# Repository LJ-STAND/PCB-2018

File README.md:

# PCB 2018

This repository contains the PCB design files for the LJ STAND 2018 robot. They were produced using Autodesk EAGLE.

**There are the following boards in the ```LJ STAND``` directory:**
- Encoder - this is a hall-sensor based encoder for the robot wheels. Each wheel has alternating polarity magnets that trigger the sensors.
- Gyro MPU9250 - this is a breakout board for a fusion of 3 MPU9250 sensors. This was done to compensate for drift
- Gyro - an older design of the IMU breakout board using a different sensor
- Laser Mount - mount for the laser in a light-gate module
- Light - a 48-sensor circular reflective-light sensor array, used for detecting the position of a white line
- Main - main processing board, housing the microcontrollers, camera, power supply, motor driver modules and IR sensors for the ball
- MPU9250 Adapter - can replace the IMU breakout board with a single off the shelf MPU9250 breakout
- Phototransitor Mount - mount for the phototransistor in a light-gate module

---------------------------------

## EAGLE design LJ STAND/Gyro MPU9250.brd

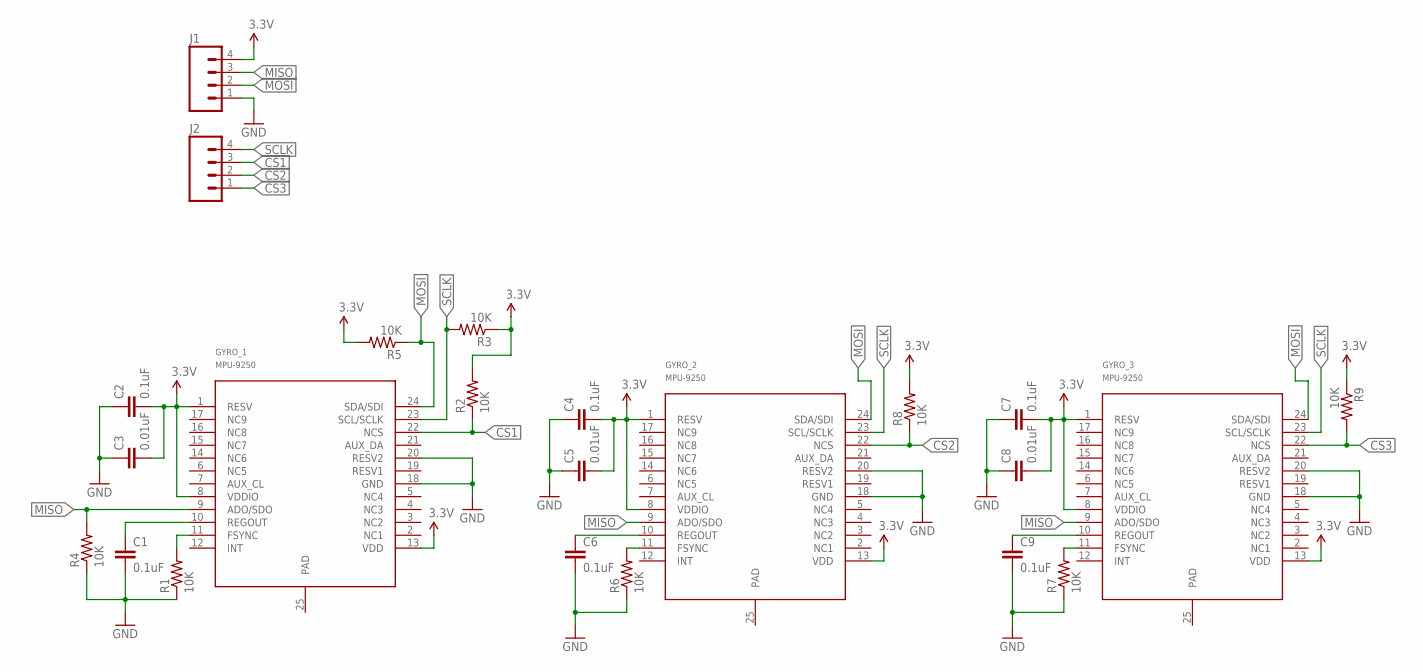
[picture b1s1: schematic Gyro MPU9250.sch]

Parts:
C1, C2, C4, C6, C7, C9: 0.1uF; 0603-CAP
C3, C5, C8: 0.01uF; 0603-CAP
GYRO_1, GYRO_2, GYRO_3: MPU-9250; LEAD-QFN24
J1, J2: M04PTH; 1X04
R1, R2, R3, R4, R5, R6, R7, R8, R9: 10K; 0603-RES

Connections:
3.3V: C2.2, C3.2, C4.2, C5.2, C7.2, C8.2, GYRO_1.1 (RESV), GYRO_1.8 (VDDIO), GYRO_1.13 (VDD), GYRO_2.1 (RESV), GYRO_2.8 (VDDIO), GYRO_2.13 (VDD), GYRO_3.1 (RESV), GYRO_3.8 (VDDIO), GYRO_3.13 (VDD), J1.4, R2.2, R3.1, R5.2, R8.2, R9.1
CS1: GYRO_1.22 (NCS), J2.3, R2.1
CS2: GYRO_2.22 (NCS), J2.2, R8.1
CS3: GYRO_3.22 (NCS), J2.1, R9.2
GND: C1.2, C2.1, C3.1, C4.1, C5.1, C6.2, C7.1, C8.1, C9.2, GYRO_1.18 (GND), GYRO_1.20 (RESV2), GYRO_2.18 (GND), GYRO_2.20 (RESV2), GYRO_3.18 (GND), GYRO_3.20 (RESV2), J1.1, R1.1, R4.1, R6.1, R7.1
MISO: GYRO_1.9 (ADO/SDO), GYRO_2.9 (ADO/SDO), GYRO_3.9 (ADO/SDO), J1.3, R4.2
MOSI: GYRO_1.24 (SDA/SDI), GYRO_2.24 (SDA/SDI), GYRO_3.24 (SDA/SDI), J1.2, R5.1
unnamed: C1.1, GYRO_1.10 (REGOUT)
unnamed: GYRO_1.11 (FSYNC), R1.2
unnamed: GYRO_3.11 (FSYNC), R7.2
unnamed: C6.1, GYRO_2.10 (REGOUT)
unnamed: C9.1, GYRO_3.10 (REGOUT)
unnamed: GYRO_2.11 (FSYNC), R6.2
SCLK: GYRO_1.23 (SCL/SCLK), GYRO_2.23 (SCL/SCLK), GYRO_3.23 (SCL/SCLK), J2.4, R3.2

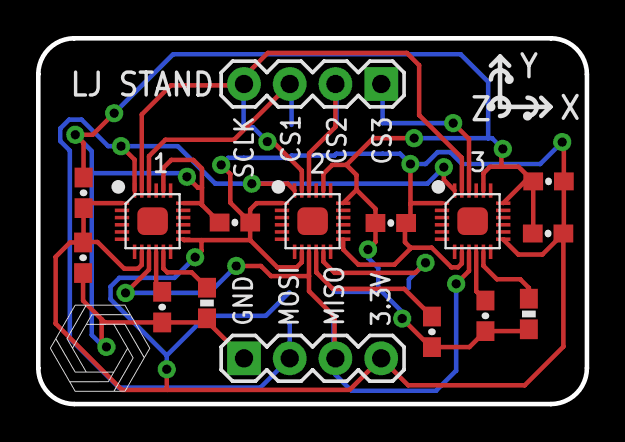
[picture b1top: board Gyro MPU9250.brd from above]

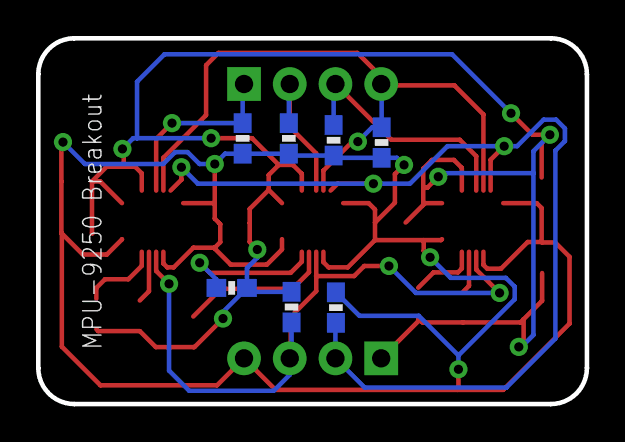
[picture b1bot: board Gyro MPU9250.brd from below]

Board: 2 copper layers, 30.5 x 20.3 mm, 23 parts (7 on the bottom side), 14 nets.

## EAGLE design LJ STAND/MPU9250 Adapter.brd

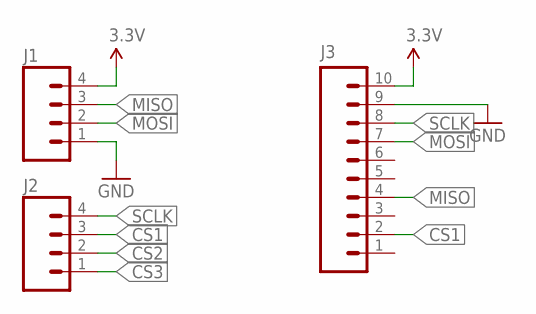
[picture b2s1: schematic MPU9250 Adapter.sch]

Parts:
J1, J2: M04PTH; 1X04
J3: M10SILK_FEMALE_PTH; 1X10

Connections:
3.3V: J1.4, J3.10
CS1: J2.3, J3.2
CS2: J2.2
CS3: J2.1
GND: J1.1, J3.9
MISO: J1.3, J3.4
MOSI: J1.2, J3.7
SCLK: J2.4, J3.8

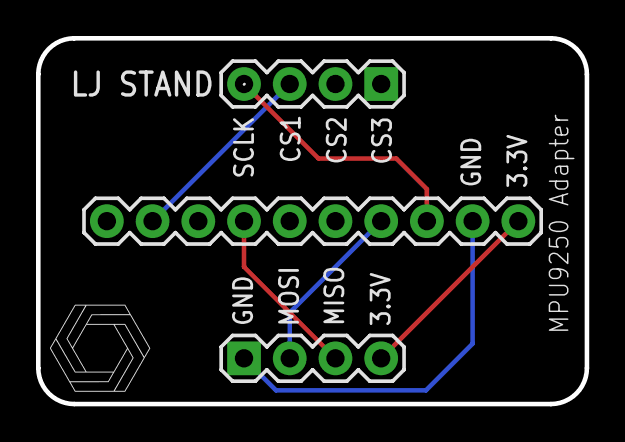
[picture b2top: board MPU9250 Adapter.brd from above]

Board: 2 copper layers, 30.5 x 20.3 mm, 3 parts (0 on the bottom side), 6 nets.

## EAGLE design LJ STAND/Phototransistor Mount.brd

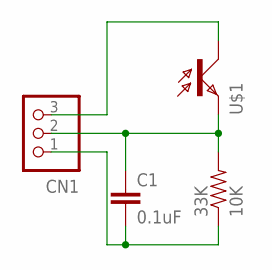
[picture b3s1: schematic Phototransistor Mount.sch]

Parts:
33K: 10K; 0603-RES
C1: 0.1uF; 0603-CAP
CN1: B3B-PH-K-S
U$1: ALS; SMD

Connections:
unnamed: CN1.3, U$1.C
unnamed: 33K.1, C1.2, CN1.1
OUT: 33K.2, C1.1, CN1.2, U$1.E

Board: 2 copper layers, 4 parts (0 on the bottom side), 3 nets, no tracks yet.

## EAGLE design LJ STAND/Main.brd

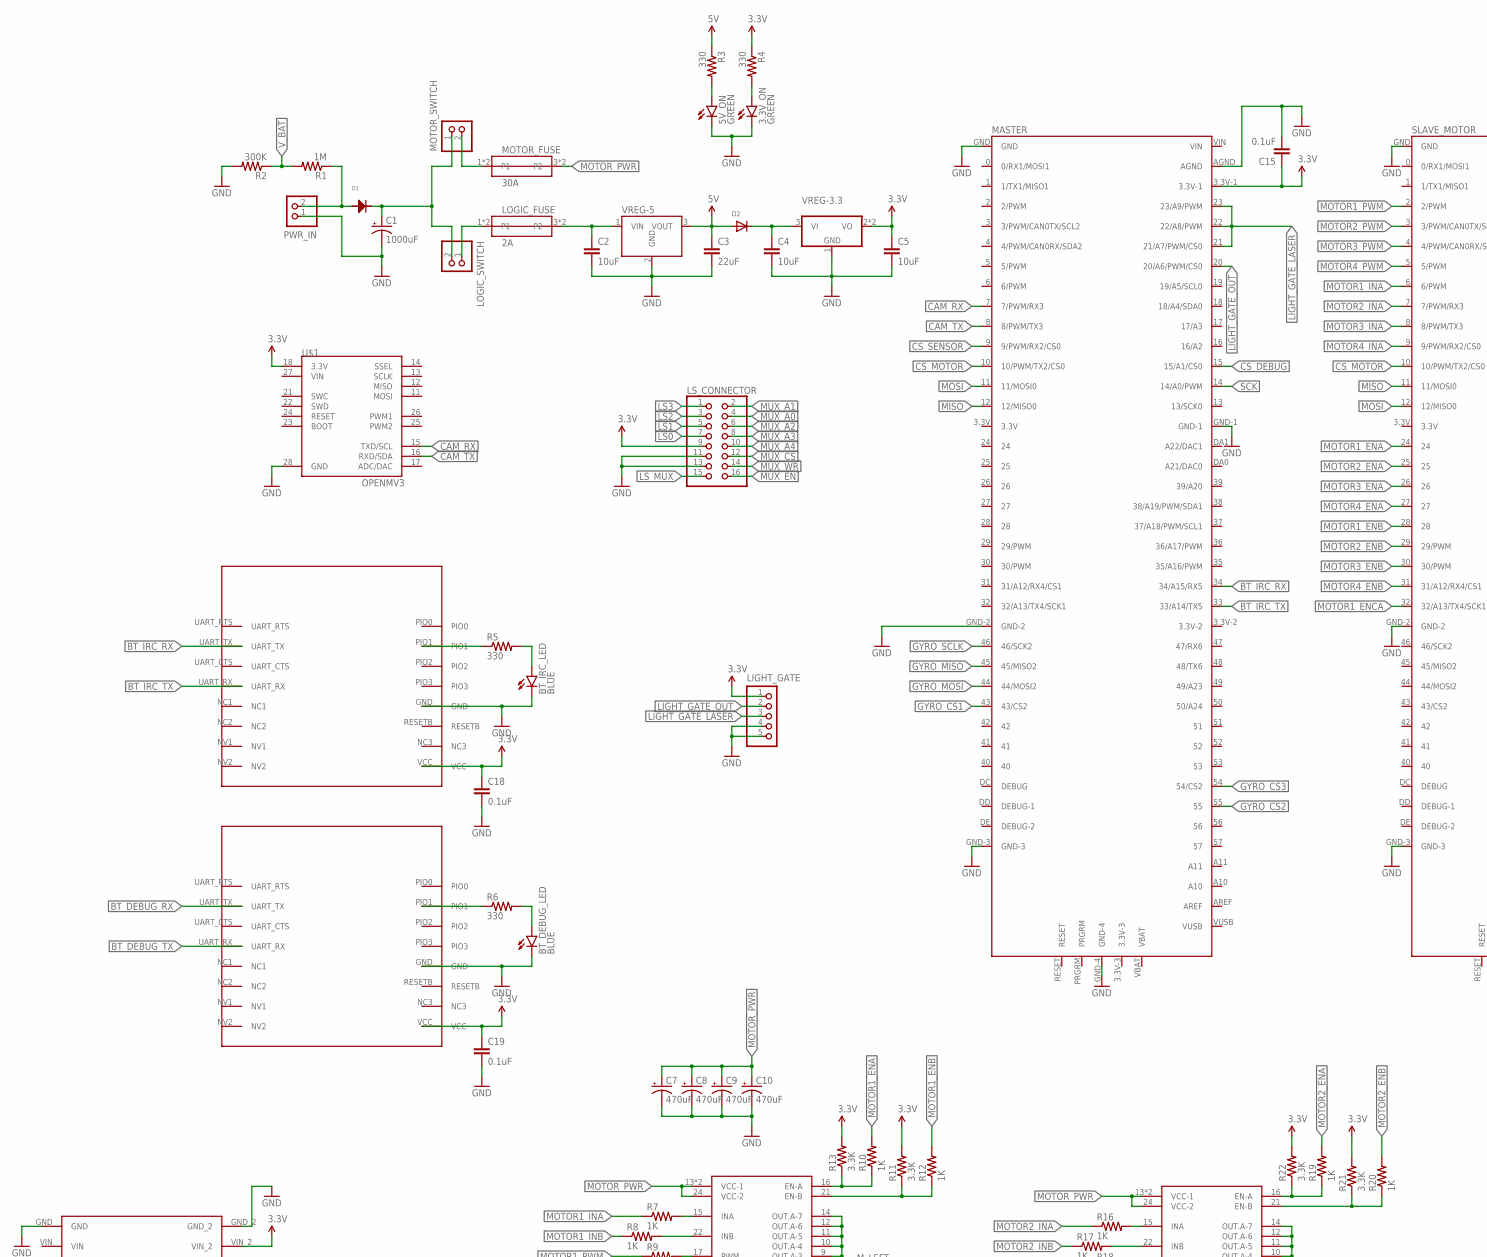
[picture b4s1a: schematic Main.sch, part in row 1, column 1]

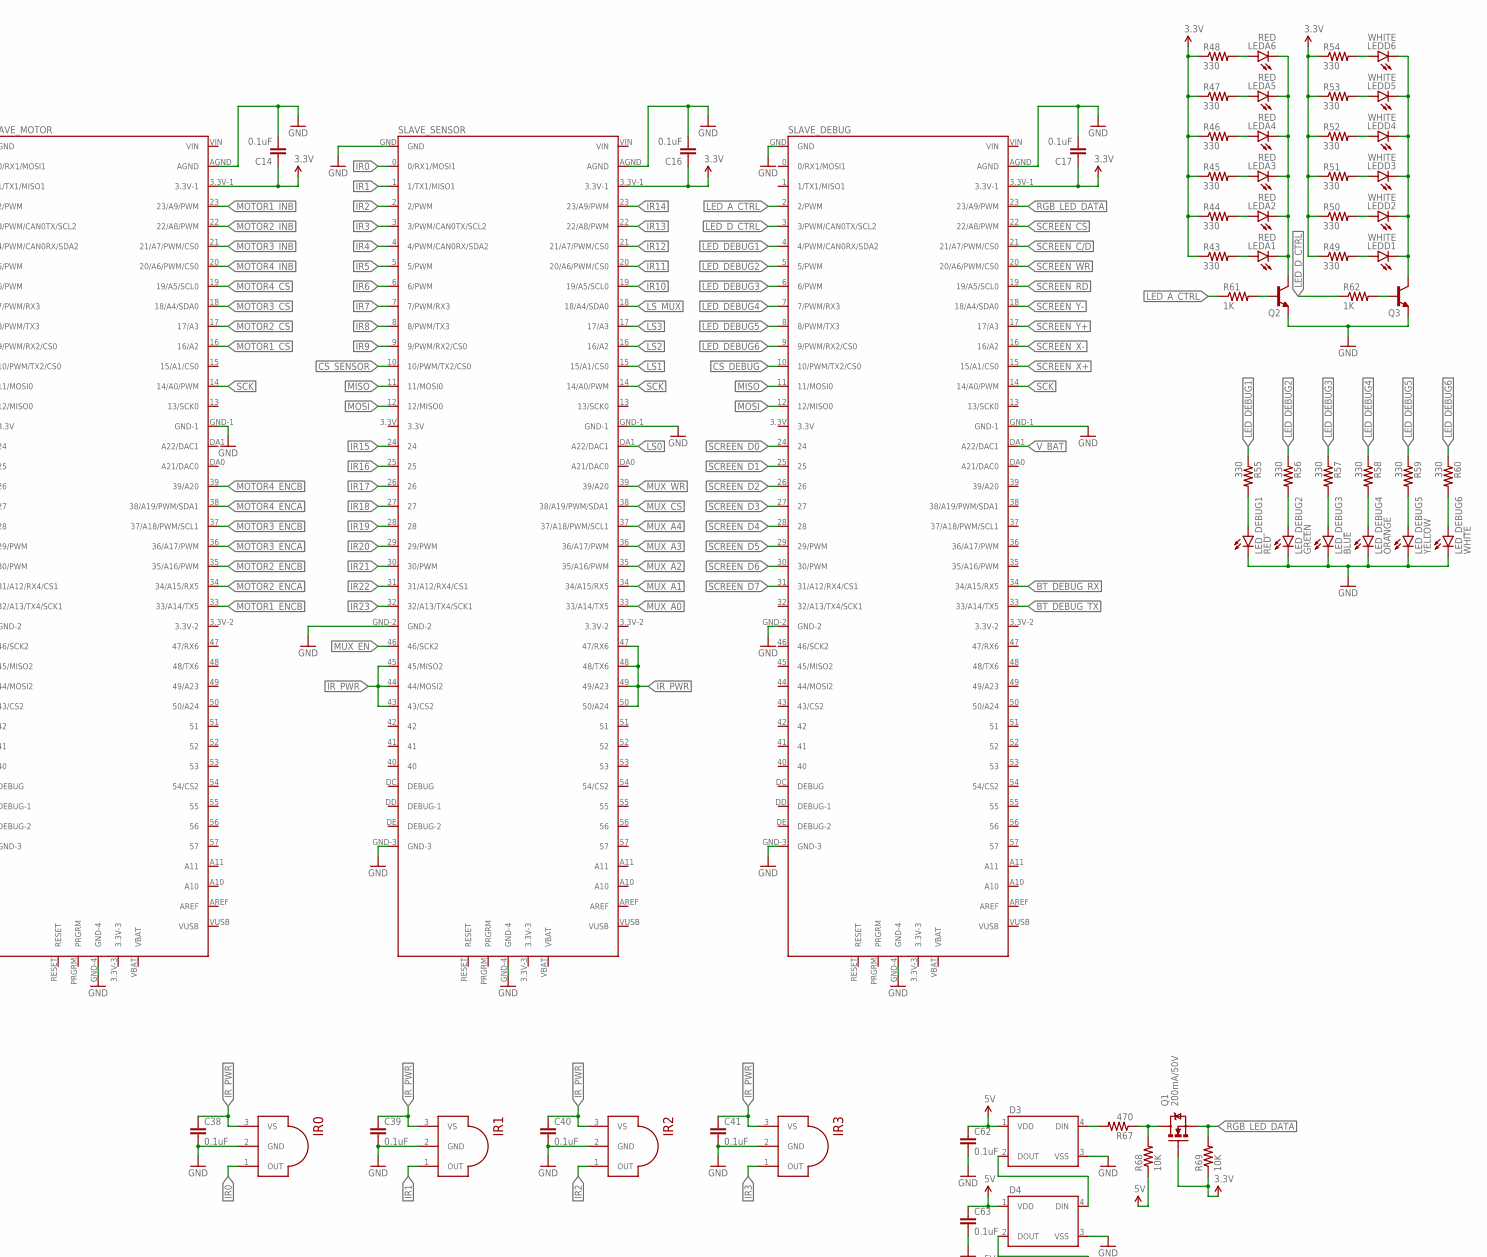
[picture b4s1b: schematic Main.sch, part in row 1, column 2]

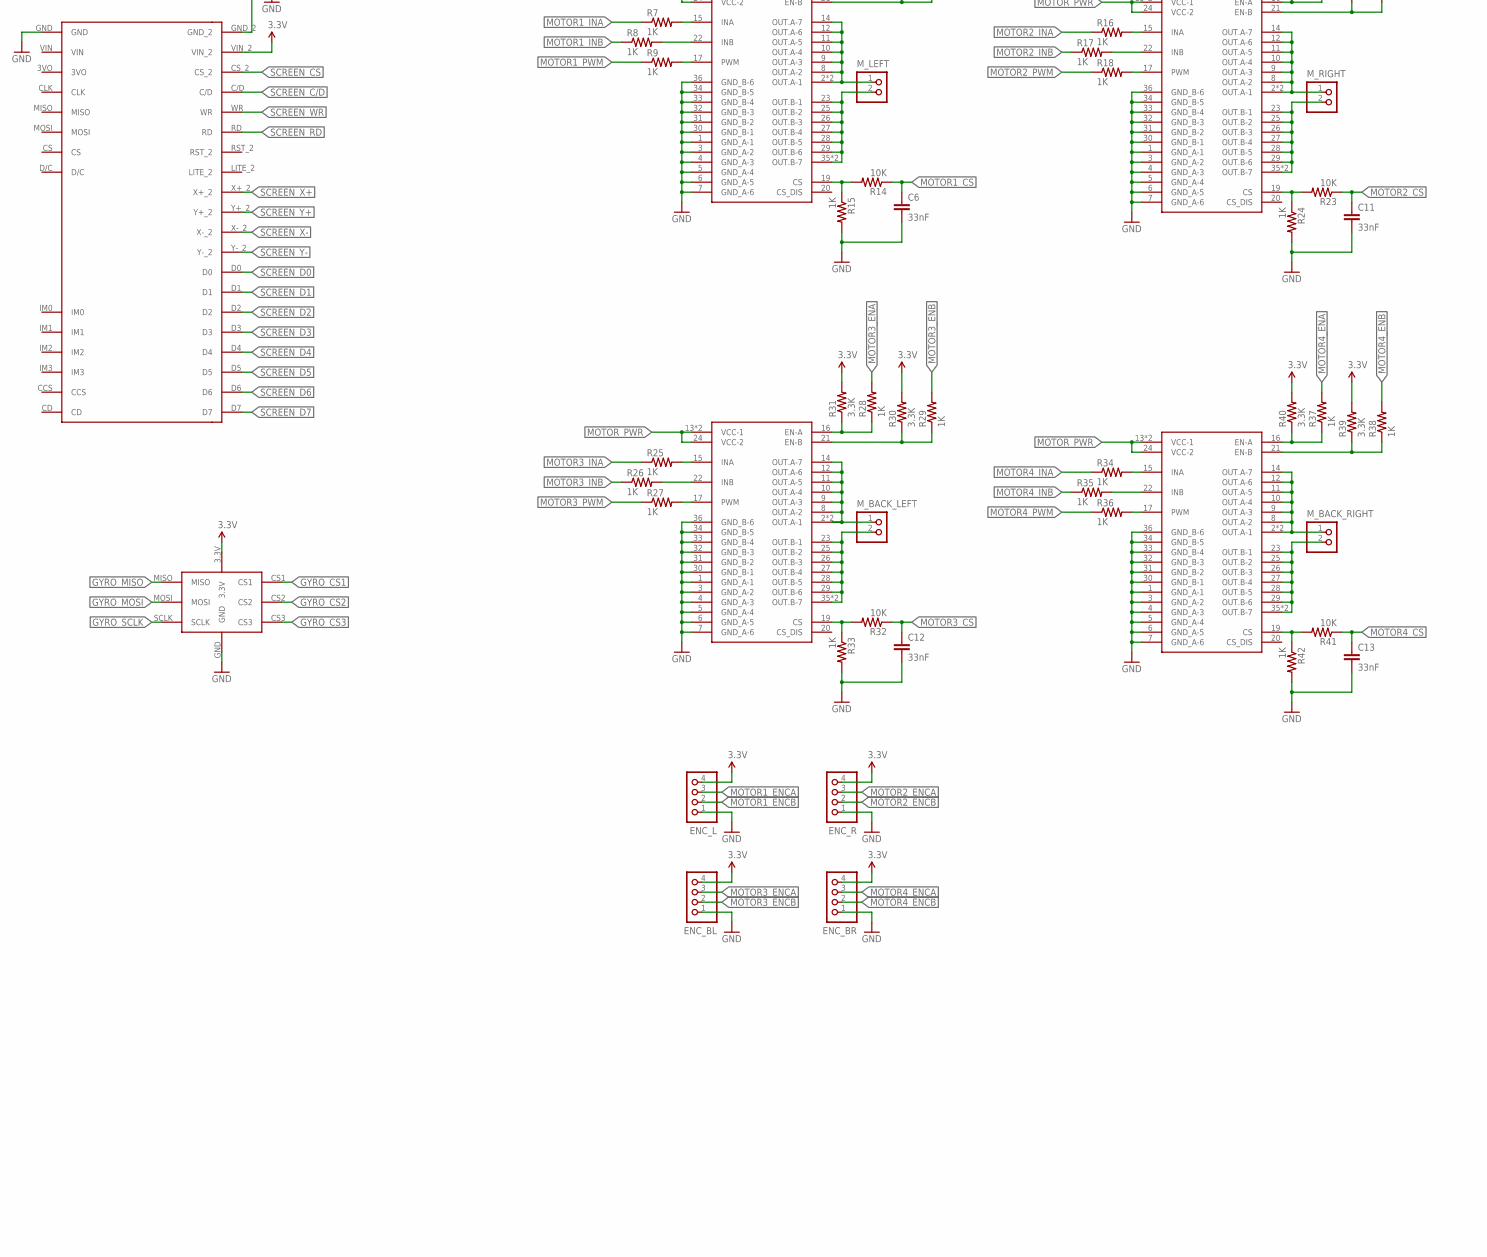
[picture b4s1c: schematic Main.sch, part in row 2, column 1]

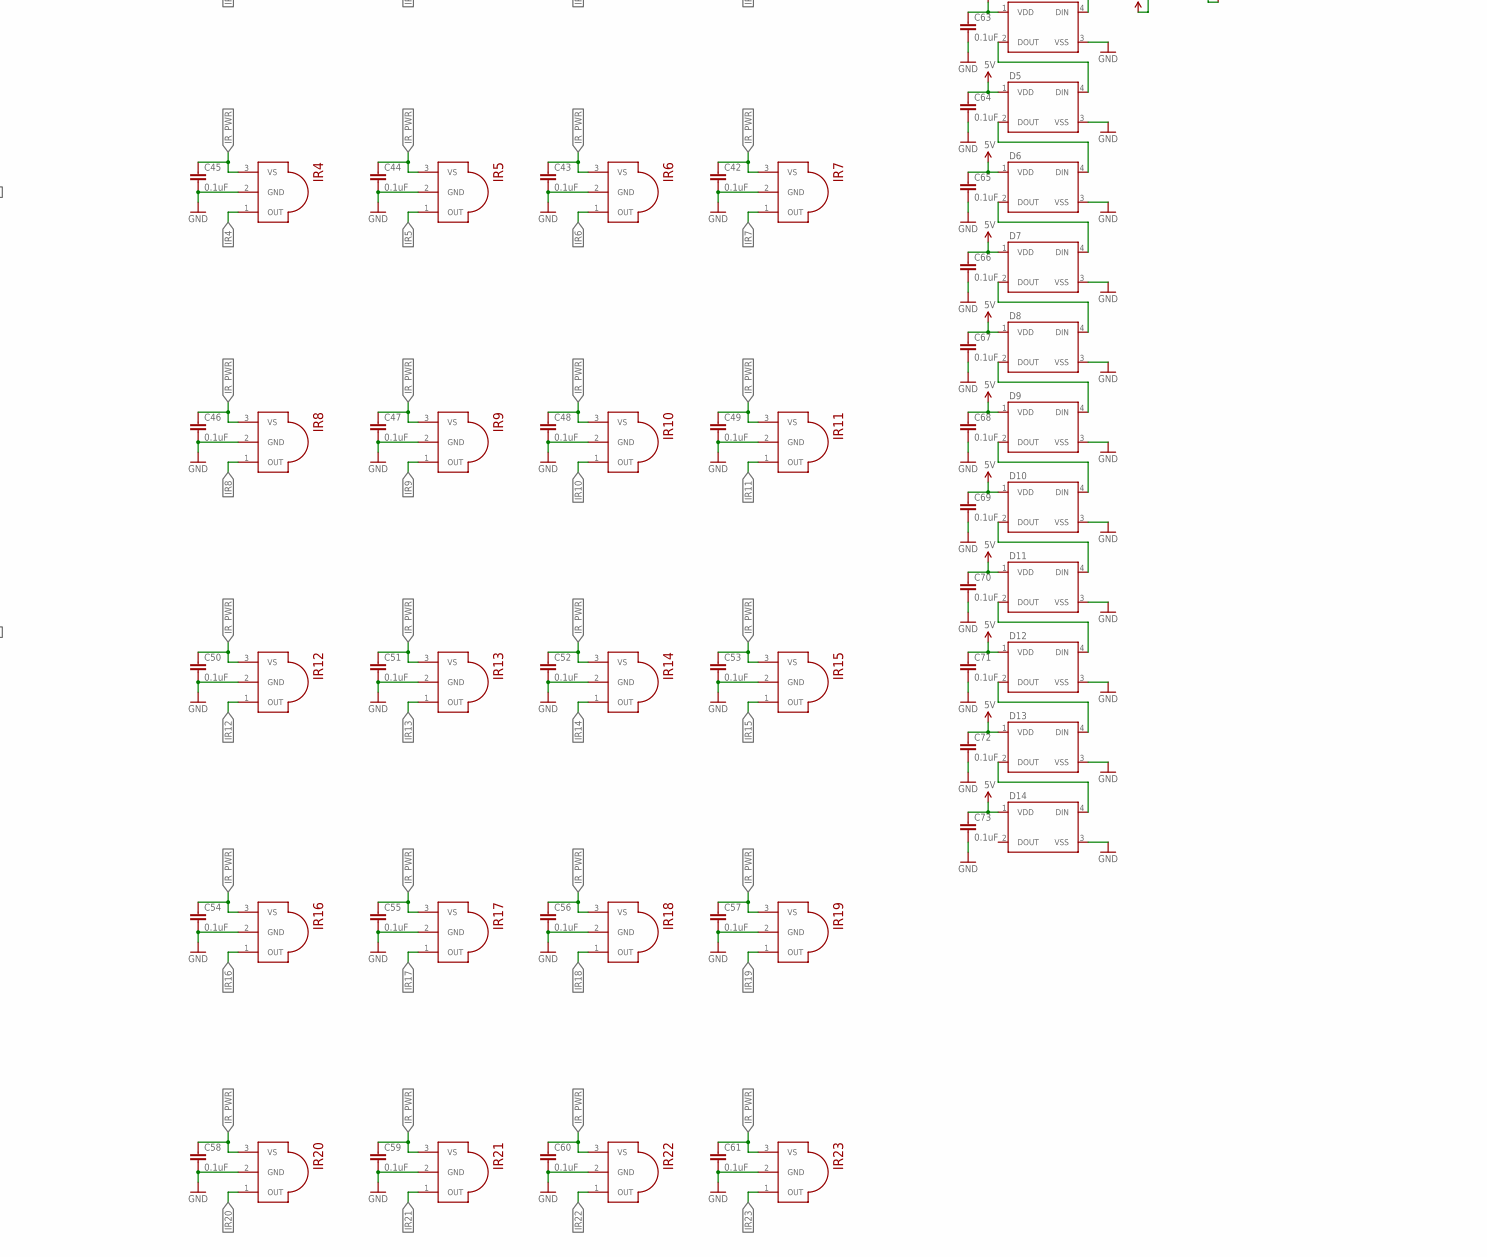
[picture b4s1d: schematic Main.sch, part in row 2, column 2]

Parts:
3.3V_ON, 5V_ON: GREEN; LED-0603
BT_DEBUG: HM-11
BT_DEBUG_LED: BLUE; LED-0603
BT_IRC: HM-11
BT_IRC_LED: BLUE; LED-0603
C1: 1000uF; CPOL-RADIAL-1000UF-25V-KIT
C2, C4, C5: 10uF; 0805
C3: 22uF; 1206
C6, C11, C12, C13: 33nF; 0603-CAP
C7, C8, C9, C10: 470uF; E3,5-8
C14, C15, C16, C17, C18, C19, C38, C39, C40, C41, C42, C43, C44, C45, C46, C47, C48, C49, C50, C51, C52, C53, C54, C55, C56, C57, C58, C59, C60, C61, C62, C63, C64, C65, C66, C67, C68, C69, C70, C71, C72, C73: 0.1uF; 0603-CAP
D1: DIODE_D2PAK(TO-263AB); D2PAK(TO-263AB)
D2: DIODE_SOD-123FL; SOD-123FL
D3, D4, D5, D6, D7, D8, D9, D10, D11, D12, D13, D14: WS2812B
ENC_BL: B4B-PH-K-S
ENC_BR: B4B-PH-K-S
ENC_L: B4B-PH-K-S
ENC_R: B4B-PH-K-S
IR0, IR1, IR2, IR3, IR4, IR5, IR6, IR7, IR8, IR9, IR10, IR11, IR12, IR13, IR14, IR15, IR16, IR17, IR18, IR19, IR20, IR21, IR22, IR23: TSSP58038
LEDA1, LEDA2, LEDA3, LEDA4, LEDA5, LEDA6: RED; LED-0603
LEDD1, LEDD2, LEDD3, LEDD4, LEDD5, LEDD6: WHITE; LED-0603
LED_DEBUG1: RED; LED-0603
LED_DEBUG2: GREEN; LED-0603
LED_DEBUG3: BLUE; LED-0603
LED_DEBUG4: ORANGE; LED-0603
LED_DEBUG5: YELLOW; LED-0603
LED_DEBUG6: WHITE; LED-0603
LIGHT_GATE: B5B-PH-K-S
LOGIC_FUSE: 2A; 3568-FUSEHOLDER
LOGIC_SWITCH: B2P-VH
LS_CONNECTOR: PINHD-2X8SMT; 2X08_SMT
MASTER: TEENSY-3.5
MOTOR_FUSE: 30A; 3568-FUSEHOLDER
MOTOR_SWITCH: B2P-VH
M_BACK_LEFT: B2P-VH
M_BACK_RIGHT: B2P-VH
M_LEFT: B2P-VH
M_RIGHT: B2P-VH
P1, P2, P3, P4: SOP50P1030X247-36N
PWR_IN: B2P-VH
Q1: 200mA/50V; SOT23-3
Q2, Q3: TRANSISTOR_NPNSOT23-3; SOT23-3
R1: 1M; 0603-RES
R2: 300K; 0603-RES
R3, R4, R5, R6, R43, R44, R45, R46, R47, R48, R49, R50, R51, R52, R53, R54, R55, R56, R57, R58, R59, R60: 330; 0603-RES
R7, R8, R9, R10, R12, R15, R16, R17, R18, R19, R20, R24, R25, R26, R27, R28, R29, R33, R34, R35, R36, R37, R38, R42, R61, R62: 1K; 0603-RES
R11, R13, R21, R22, R30, R31, R39, R40: 3.3K; 0603-RES
R14, R23, R32, R41, R68, R69: 10K; 0603-RES
R67: 470; 0603-RES
SCREEN: ADAFRUIT-2.4-TFT
SLAVE_DEBUG: TEENSY-3.5
SLAVE_MOTOR: TEENSY-3.5
SLAVE_SENSOR: TEENSY-3.5
U$1: OPENMV3
U$2: GYRO
VREG-3.3: LM340S-05; TO263-3
VREG-5: V78-2000

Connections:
3.3V: BT_DEBUG.VCC, BT_IRC.VCC, C5.1, C14.1, C15.1, C16.1, C17.1, C18.1, C19.1, ENC_BL.4, ENC_BR.4, ENC_L.4, ENC_R.4, LIGHT_GATE.1, LS_CONNECTOR.9, MASTER.3.3V-1, Q1.1 (G), R4.1, R11.2, R13.2, R21.2, R22.2, R30.2, R31.2, R39.2, R40.2, R43.1, R44.1, R45.1, R46.1, R47.1, R48.1, R49.1, R50.1, R51.1, R52.1, R53.1, R54.1, R69.1, SCREEN.VIN_2, SLAVE_DEBUG.3.3V-1, SLAVE_MOTOR.3.3V-1, SLAVE_SENSOR.3.3V-1, U$1.18 (3.3V), U$2.3.3V, VREG-3.3.2 (VO), VREG-3.3.TAB (VO)
5V: C3.1, C62.1, C63.1, C64.1, C65.1, C66.1, C67.1, C68.1, C69.1, C70.1, C71.1, C72.1, C73.1, D2.A, D3.1 (VDD), D4.1 (VDD), D5.1 (VDD), D6.1 (VDD), D7.1 (VDD), D8.1 (VDD), D9.1 (VDD), D10.1 (VDD), D11.1 (VDD), D12.1 (VDD), D13.1 (VDD), D14.1 (VDD), R3.1, R68.1, VREG-5.3 (VOUT)
BT_DEBUG_RX: BT_DEBUG.UART_TX, SLAVE_DEBUG.34 (34/A15/RX5)
BT_DEBUG_TX: BT_DEBUG.UART_RX, SLAVE_DEBUG.33 (33/A14/TX5)
BT_IRC_RX: BT_IRC.UART_TX, MASTER.34 (34/A15/RX5)
BT_IRC_TX: BT_IRC.UART_RX, MASTER.33 (33/A14/TX5)
CAM_RX: MASTER.7 (7/PWM/RX3), U$1.15 (TXD/SCL)
CAM_TX: MASTER.8 (8/PWM/TX3), U$1.16 (RXD/SDA)
CS_DEBUG: MASTER.15 (15/A1/CS0), SLAVE_DEBUG.10 (10/PWM/TX2/CS0)
CS_MOTOR: MASTER.10 (10/PWM/TX2/CS0), SLAVE_MOTOR.10 (10/PWM/TX2/CS0)
CS_SENSOR: MASTER.9 (9/PWM/RX2/CS0), SLAVE_SENSOR.10 (10/PWM/TX2/CS0)
GND: 3.3V_ON.C, 5V_ON.C, BT_DEBUG.GND, BT_DEBUG_LED.C, BT_IRC.GND, BT_IRC_LED.C, C1.-, C2.2, C3.2, C4.2, C5.2, C6.2, C7.-, C8.-, C9.-, C10.-, C11.2, C12.2, C13.2, C14.2, C15.2, C16.2, C17.2, C18.2, C19.2, C38.2, C39.2, C40.2, C41.2, C42.2, C43.2, C44.2, C45.2, C46.2, C47.2, C48.2, C49.2, C50.2, C51.2, C52.2, C53.2, C54.2, C55.2, C56.2, C57.2, C58.2, C59.2, C60.2, C61.2, C62.2, C63.2, C64.2, C65.2, C66.2, C67.2, C68.2, C69.2, C70.2, C71.2, C72.2, C73.2, D3.3 (VSS), D4.3 (VSS), D5.3 (VSS), D6.3 (VSS), D7.3 (VSS), D8.3 (VSS), D9.3 (VSS), D10.3 (VSS), D11.3 (VSS), D12.3 (VSS), D13.3 (VSS), D14.3 (VSS), ENC_BL.1, ENC_BR.1, ENC_L.1, ENC_R.1, IR0.2 (GND), IR1.2 (GND), IR2.2 (GND), IR3.2 (GND), IR4.2 (GND), IR5.2 (GND), IR6.2 (GND), IR7.2 (GND), IR8.2 (GND), IR9.2 (GND), IR10.2 (GND), IR11.2 (GND), IR12.2 (GND), IR13.2 (GND), IR14.2 (GND), IR15.2 (GND), IR16.2 (GND), IR17.2 (GND), IR18.2 (GND), IR19.2 (GND), IR20.2 (GND), IR21.2 (GND), IR22.2 (GND), IR23.2 (GND), LED_DEBUG1.C, LED_DEBUG2.C, LED_DEBUG3.C, LED_DEBUG4.C, LED_DEBUG5.C, LED_DEBUG6.C, LIGHT_GATE.4, LIGHT_GATE.5, LS_CONNECTOR.11, LS_CONNECTOR.13, MASTER.AGND, MASTER.GND, MASTER.GND-1, MASTER.GND-2, MASTER.GND-3, MASTER.GND-4, P1.1 (GND_A-1), P1.3 (GND_A-2), P1.4 (GND_A-3), P1.5 (GND_A-4), P1.6 (GND_A-5), P1.7 (GND_A-6), P1.30 (GND_B-1), P1.31 (GND_B-2), P1.32 (GND_B-3), P1.33 (GND_B-4), P1.34 (GND_B-5), P1.36 (GND_B-6), P2.1 (GND_A-1), P2.3 (GND_A-2), P2.4 (GND_A-3), P2.5 (GND_A-4), P2.6 (GND_A-5), P2.7 (GND_A-6), P2.30 (GND_B-1), P2.31 (GND_B-2), P2.32 (GND_B-3), P2.33 (GND_B-4), P2.34 (GND_B-5)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
GYRO_CS1: MASTER.43 (43/CS2), U$2.CS1
GYRO_CS2: MASTER.55, U$2.CS2
GYRO_CS3: MASTER.54 (54/CS2), U$2.CS3
GYRO_MISO: MASTER.45 (45/MISO2), U$2.MISO
GYRO_MOSI: MASTER.44 (44/MOSI2), U$2.MOSI
GYRO_SCLK: MASTER.46 (46/SCK2), U$2.SCLK
IR0: IR0.1 (OUT), SLAVE_SENSOR.0 (0/RX1/MOSI1)
IR1: IR1.1 (OUT), SLAVE_SENSOR.1 (1/TX1/MISO1)
IR2: IR2.1 (OUT), SLAVE_SENSOR.2 (2/PWM)
IR3: IR3.1 (OUT), SLAVE_SENSOR.3 (3/PWM/CAN0TX/SCL2)
IR4: IR4.1 (OUT), SLAVE_SENSOR.4 (4/PWM/CAN0RX/SDA2)
IR5: IR5.1 (OUT), SLAVE_SENSOR.5 (5/PWM)
IR6: IR6.1 (OUT), SLAVE_SENSOR.6 (6/PWM)
IR7: IR7.1 (OUT), SLAVE_SENSOR.7 (7/PWM/RX3)
IR8: IR8.1 (OUT), SLAVE_SENSOR.8 (8/PWM/TX3)
IR9: IR9.1 (OUT), SLAVE_SENSOR.9 (9/PWM/RX2/CS0)
IR10: IR10.1 (OUT), SLAVE_SENSOR.19 (19/A5/SCL0)
IR11: IR11.1 (OUT), SLAVE_SENSOR.20 (20/A6/PWM/CS0)
IR12: IR12.1 (OUT), SLAVE_SENSOR.21 (21/A7/PWM/CS0)
IR13: IR13.1 (OUT), SLAVE_SENSOR.22 (22/A8/PWM)
IR14: IR14.1 (OUT), SLAVE_SENSOR.23 (23/A9/PWM)
IR15: IR15.1 (OUT), SLAVE_SENSOR.24
IR16: IR16.1 (OUT), SLAVE_SENSOR.25
IR17: IR17.1 (OUT), SLAVE_SENSOR.26
IR18: IR18.1 (OUT), SLAVE_SENSOR.27
IR19: IR19.1 (OUT), SLAVE_SENSOR.28
IR20: IR20.1 (OUT), SLAVE_SENSOR.29 (29/PWM)
IR21: IR21.1 (OUT), SLAVE_SENSOR.30 (30/PWM)
IR22: IR22.1 (OUT), SLAVE_SENSOR.31 (31/A12/RX4/CS1)
IR23: IR23.1 (OUT), SLAVE_SENSOR.32 (32/A13/TX4/SCK1)
IR_PWR: C38.1, C39.1, C40.1, C41.1, C42.1, C43.1, C44.1, C45.1, C46.1, C47.1, C48.1, C49.1, C50.1, C51.1, C52.1, C53.1, C54.1, C55.1, C56.1, C57.1, C58.1, C59.1, C60.1, C61.1, IR0.3 (VS), IR1.3 (VS), IR2.3 (VS), IR3.3 (VS), IR4.3 (VS), IR5.3 (VS), IR6.3 (VS), IR7.3 (VS), IR8.3 (VS), IR9.3 (VS), IR10.3 (VS), IR11.3 (VS), IR12.3 (VS), IR13.3 (VS), IR14.3 (VS), IR15.3 (VS), IR16.3 (VS), IR17.3 (VS), IR18.3 (VS), IR19.3 (VS), IR20.3 (VS), IR21.3 (VS), IR22.3 (VS), IR23.3 (VS), SLAVE_SENSOR.43 (43/CS2), SLAVE_SENSOR.44 (44/MOSI2), SLAVE_SENSOR.45 (45/MISO2), SLAVE_SENSOR.47 (47/RX6), SLAVE_SENSOR.48 (48/TX6), SLAVE_SENSOR.49 (49/A23), SLAVE_SENSOR.50 (50/A24)
LED_A_CTRL: R61.1, SLAVE_DEBUG.2 (2/PWM)
LED_DEBUG1: R55.1, SLAVE_DEBUG.4 (4/PWM/CAN0RX/SDA2)
LED_DEBUG2: R56.1, SLAVE_DEBUG.5 (5/PWM)
LED_DEBUG3: R57.1, SLAVE_DEBUG.6 (6/PWM)
LED_DEBUG4: R58.1, SLAVE_DEBUG.7 (7/PWM/RX3)
LED_DEBUG5: R59.1, SLAVE_DEBUG.8 (8/PWM/TX3)
LED_DEBUG6: R60.1, SLAVE_DEBUG.9 (9/PWM/RX2/CS0)
LED_D_CTRL: R62.1, SLAVE_DEBUG.3 (3/PWM/CAN0TX/SCL2)
LIGHT_GATE_LASER: LIGHT_GATE.3, MASTER.21 (21/A7/PWM/CS0), MASTER.22 (22/A8/PWM), MASTER.23 (23/A9/PWM)
LIGHT_GATE_OUT: LIGHT_GATE.2, MASTER.20 (20/A6/PWM/CS0)
LS0: LS_CONNECTOR.7, SLAVE_SENSOR.DA1 (A22/DAC1)
LS1: LS_CONNECTOR.5, SLAVE_SENSOR.15 (15/A1/CS0)
LS2: LS_CONNECTOR.3, SLAVE_SENSOR.16 (16/A2)
LS3: LS_CONNECTOR.1, SLAVE_SENSOR.17 (17/A3)
LS_MUX: LS_CONNECTOR.15, SLAVE_SENSOR.18 (18/A4/SDA0)
MISO: MASTER.12 (12/MISO0), SLAVE_DEBUG.11 (11/MOSI0), SLAVE_MOTOR.11 (11/MOSI0), SLAVE_SENSOR.11 (11/MOSI0)
MOSI: MASTER.11 (11/MOSI0), SLAVE_DEBUG.12 (12/MISO0), SLAVE_MOTOR.12 (12/MISO0), SLAVE_SENSOR.12 (12/MISO0)
MOTOR1_CS: C6.1, R14.1, SLAVE_MOTOR.16 (16/A2)
MOTOR1_ENA: R10.2, SLAVE_MOTOR.24
MOTOR1_ENB: R12.2, SLAVE_MOTOR.28
MOTOR1_ENCA: ENC_L.3, SLAVE_MOTOR.32 (32/A13/TX4/SCK1)
MOTOR1_ENCB: ENC_L.2, SLAVE_MOTOR.33 (33/A14/TX5)
MOTOR1_INA: R7.1, SLAVE_MOTOR.6 (6/PWM)
MOTOR1_INB: R8.1, SLAVE_MOTOR.23 (23/A9/PWM)
MOTOR1_OUTA: M_LEFT.1, P1.2 (OUT.A-1), P1.8 (OUT.A-2), P1.9 (OUT.A-3), P1.10 (OUT.A-4), P1.11 (OUT.A-5), P1.12 (OUT.A-6), P1.14 (OUT.A-7), P1.SLUG2 (OUT.A-1); also elsewhere on the board
MOTOR1_OUTB: M_LEFT.2, P1.23 (OUT.B-1), P1.25 (OUT.B-2), P1.26 (OUT.B-3), P1.27 (OUT.B-4), P1.28 (OUT.B-5), P1.29 (OUT.B-6), P1.35 (OUT.B-7), P1.SLUG3 (OUT.B-7); also elsewhere on the board
MOTOR1_PWM: R9.1, SLAVE_MOTOR.2 (2/PWM)
MOTOR2_CS: C11.1, R23.1, SLAVE_MOTOR.17 (17/A3)
MOTOR2_ENA: R19.2, SLAVE_MOTOR.25
MOTOR2_ENB: R20.2, SLAVE_MOTOR.29 (29/PWM)
MOTOR2_ENCA: ENC_R.3, SLAVE_MOTOR.34 (34/A15/RX5)
MOTOR2_ENCB: ENC_R.2, SLAVE_MOTOR.35 (35/A16/PWM)
MOTOR2_INA: R16.1, SLAVE_MOTOR.7 (7/PWM/RX3)
MOTOR2_INB: R17.1, SLAVE_MOTOR.22 (22/A8/PWM)
MOTOR2_OUTA: M_RIGHT.1, P2.2 (OUT.A-1), P2.8 (OUT.A-2), P2.9 (OUT.A-3), P2.10 (OUT.A-4), P2.11 (OUT.A-5), P2.12 (OUT.A-6), P2.14 (OUT.A-7), P2.SLUG2 (OUT.A-1); also elsewhere on the board
MOTOR2_OUTB: M_RIGHT.2, P2.23 (OUT.B-1), P2.25 (OUT.B-2), P2.26 (OUT.B-3), P2.27 (OUT.B-4), P2.28 (OUT.B-5), P2.29 (OUT.B-6), P2.35 (OUT.B-7), P2.SLUG3 (OUT.B-7); also elsewhere on the board
MOTOR2_PWM: R18.1, SLAVE_MOTOR.3 (3/PWM/CAN0TX/SCL2)
MOTOR3_CS: C12.1, R32.1, SLAVE_MOTOR.18 (18/A4/SDA0)
MOTOR3_ENA: R28.2, SLAVE_MOTOR.26
MOTOR3_ENB: R29.2, SLAVE_MOTOR.30 (30/PWM)
MOTOR3_ENCA: ENC_BL.3, SLAVE_MOTOR.36 (36/A17/PWM)
MOTOR3_ENCB: ENC_BL.2, SLAVE_MOTOR.37 (37/A18/PWM/SCL1)
MOTOR3_INA: R25.1, SLAVE_MOTOR.8 (8/PWM/TX3)
MOTOR3_INB: R26.1, SLAVE_MOTOR.21 (21/A7/PWM/CS0)
MOTOR3_OUTA: M_BACK_LEFT.1, P3.2 (OUT.A-1), P3.8 (OUT.A-2), P3.9 (OUT.A-3), P3.10 (OUT.A-4), P3.11 (OUT.A-5), P3.12 (OUT.A-6), P3.14 (OUT.A-7), P3.SLUG2 (OUT.A-1); also elsewhere on the board
MOTOR3_OUTB: M_BACK_LEFT.2, P3.23 (OUT.B-1), P3.25 (OUT.B-2), P3.26 (OUT.B-3), P3.27 (OUT.B-4), P3.28 (OUT.B-5), P3.29 (OUT.B-6), P3.35 (OUT.B-7), P3.SLUG3 (OUT.B-7); also elsewhere on the board
MOTOR3_PWM: R27.1, SLAVE_MOTOR.4 (4/PWM/CAN0RX/SDA2)
MOTOR4_CS: C13.1, R41.1, SLAVE_MOTOR.19 (19/A5/SCL0)
MOTOR4_ENA: R37.2, SLAVE_MOTOR.27
MOTOR4_ENB: R38.2, SLAVE_MOTOR.31 (31/A12/RX4/CS1)
MOTOR4_ENCA: ENC_BR.3, SLAVE_MOTOR.38 (38/A19/PWM/SDA1)
MOTOR4_ENCB: ENC_BR.2, SLAVE_MOTOR.39 (39/A20)
MOTOR4_INA: R34.1, SLAVE_MOTOR.9 (9/PWM/RX2/CS0)
MOTOR4_INB: R35.1, SLAVE_MOTOR.20 (20/A6/PWM/CS0)
MOTOR4_OUTA: M_BACK_RIGHT.1, P4.2 (OUT.A-1), P4.8 (OUT.A-2), P4.9 (OUT.A-3), P4.10 (OUT.A-4), P4.11 (OUT.A-5), P4.12 (OUT.A-6), P4.14 (OUT.A-7), P4.SLUG2 (OUT.A-1); also elsewhere on the board
MOTOR4_OUTB: M_BACK_RIGHT.2, P4.23 (OUT.B-1), P4.25 (OUT.B-2), P4.26 (OUT.B-3), P4.27 (OUT.B-4), P4.28 (OUT.B-5), P4.29 (OUT.B-6), P4.35 (OUT.B-7), P4.SLUG3 (OUT.B-7); also elsewhere on the board
MOTOR4_PWM: R36.1, SLAVE_MOTOR.5 (5/PWM)
MOTOR_PWR: C7.+, C8.+, C9.+, C10.+, MOTOR_FUSE.3 (P2), MOTOR_FUSE.4 (P2), P1.13 (VCC-1), P1.24 (VCC-2), P1.SLUG1 (VCC-1), P2.13 (VCC-1), P2.24 (VCC-2), P2.SLUG1 (VCC-1), P3.13 (VCC-1), P3.24 (VCC-2), P3.SLUG1 (VCC-1), P4.13 (VCC-1), P4.24 (VCC-2), P4.SLUG1 (VCC-1)
MUX_A0: LS_CONNECTOR.4, SLAVE_SENSOR.33 (33/A14/TX5)
MUX_A1: LS_CONNECTOR.2, SLAVE_SENSOR.34 (34/A15/RX5)
MUX_A2: LS_CONNECTOR.6, SLAVE_SENSOR.35 (35/A16/PWM)
MUX_A3: LS_CONNECTOR.8, SLAVE_SENSOR.36 (36/A17/PWM)
MUX_A4: LS_CONNECTOR.10, SLAVE_SENSOR.37 (37/A18/PWM/SCL1)
MUX_CS: LS_CONNECTOR.12, SLAVE_SENSOR.38 (38/A19/PWM/SDA1)
MUX_EN: LS_CONNECTOR.16, SLAVE_SENSOR.46 (46/SCK2)
MUX_WR: LS_CONNECTOR.14, SLAVE_SENSOR.39 (39/A20)
unnamed: MOTOR_FUSE.1, MOTOR_FUSE.2 (P1), MOTOR_SWITCH.2
unnamed: LOGIC_FUSE.1, LOGIC_FUSE.2 (P1), LOGIC_SWITCH.1
unnamed: LEDA1.A, R43.2
unnamed: LEDA2.A, R44.2
unnamed: LEDA3.A, R45.2
unnamed: LEDA4.A, R46.2
unnamed: LEDA5.A, R47.2
unnamed: LEDA6.A, R48.2
unnamed: LEDA1.C, LEDA2.C, LEDA3.C, LEDA4.C, LEDA5.C, LEDA6.C, Q2.3 (C)
unnamed: D1.A (ANODE), D1.NOP (ANODE), PWR_IN.2, R1.1
unnamed: C1.+, D1.C (CATHODE), LOGIC_SWITCH.2, MOTOR_SWITCH.1
unnamed: C2.1, LOGIC_FUSE.3 (P2), LOGIC_FUSE.4 (P2), VREG-5.1 (VIN)
unnamed: C4.1, D2.C, VREG-3.3.3 (VI)
unnamed: 5V_ON.A, R3.2
unnamed: 3.3V_ON.A, R4.2
unnamed: BT_IRC_LED.A, R5.2
unnamed: BT_IRC.PIO1, R5.1
unnamed: BT_DEBUG_LED.A, R6.2
unnamed: BT_DEBUG.PIO1, R6.1
unnamed: P1.16 (EN-A), R10.1, R13.1
unnamed: P1.22 (INB), R8.2
unnamed: P1.17 (PWM), R9.2
unnamed: P1.15 (INA), R7.2
unnamed: P1.21 (EN-B), R11.1, R12.1
unnamed: P1.19 (CS), R14.2, R15.1
unnamed: LEDD1.A, R49.2
unnamed: P2.15 (INA), R16.2
unnamed: P2.22 (INB), R17.2
unnamed: P2.17 (PWM), R18.2
unnamed: P2.16 (EN-A), R19.1, R22.1
unnamed: P2.21 (EN-B), R20.1, R21.1
unnamed: P2.19 (CS), R23.2, R24.1
unnamed: P3.15 (INA), R25.2
unnamed: P3.22 (INB), R26.2
unnamed: P3.17 (PWM), R27.2
unnamed: P3.16 (EN-A), R28.1, R31.1
unnamed: P3.21 (EN-B), R29.1, R30.1
unnamed: P3.19 (CS), R32.2, R33.1
unnamed: P4.15 (INA), R34.2
unnamed: P4.22 (INB), R35.2
unnamed: P4.17 (PWM), R36.2
unnamed: P4.16 (EN-A), R37.1, R40.1
unnamed: P4.21 (EN-B), R38.1, R39.1
unnamed: P4.19 (CS), R41.2, R42.1
unnamed: LEDD2.A, R50.2
unnamed: LEDD3.A, R51.2
unnamed: LEDD4.A, R52.2
unnamed: LEDD5.A, R53.2
unnamed: LEDD6.A, R54.2
unnamed: LEDD1.C, LEDD2.C, LEDD3.C, LEDD4.C, LEDD5.C, LEDD6.C, Q3.3 (C)
unnamed: LED_DEBUG1.A, R55.2
unnamed: LED_DEBUG2.A, R56.2
unnamed: LED_DEBUG3.A, R57.2
unnamed: LED_DEBUG4.A, R58.2
unnamed: LED_DEBUG5.A, R59.2
unnamed: LED_DEBUG6.A, R60.2
unnamed: Q2.1 (B), R61.2
unnamed: Q3.1 (B), R62.2
unnamed: D3.2 (DOUT), D4.4 (DIN)
unnamed: D4.2 (DOUT), D5.4 (DIN)
unnamed: D5.2 (DOUT), D6.4 (DIN)
unnamed: D6.2 (DOUT), D7.4 (DIN)
unnamed: D7.2 (DOUT), D8.4 (DIN)
unnamed: D8.2 (DOUT), D9.4 (DIN)
unnamed: D9.2 (DOUT), D10.4 (DIN)
unnamed: D10.2 (DOUT), D11.4 (DIN)
unnamed: D11.2 (DOUT), D12.4 (DIN)
unnamed: D12.2 (DOUT), D13.4 (DIN)
unnamed: D13.2 (DOUT), D14.4 (DIN)
unnamed: Q1.3 (D), R67.1, R68.2
unnamed: D3.4 (DIN), R67.2
RGB_LED_DATA: Q1.2 (S), R69.2, SLAVE_DEBUG.23 (23/A9/PWM)
SCK: MASTER.14 (14/A0/PWM), SLAVE_DEBUG.14 (14/A0/PWM), SLAVE_MOTOR.14 (14/A0/PWM), SLAVE_SENSOR.14 (14/A0/PWM)
SCREEN_C/D: SCREEN.C/D, SLAVE_DEBUG.21 (21/A7/PWM/CS0)
SCREEN_CS: SCREEN.CS_2, SLAVE_DEBUG.22 (22/A8/PWM)
SCREEN_D0: SCREEN.D0, SLAVE_DEBUG.24
SCREEN_D1: SCREEN.D1, SLAVE_DEBUG.25
SCREEN_D2: SCREEN.D2, SLAVE_DEBUG.26
SCREEN_D3: SCREEN.D3, SLAVE_DEBUG.27
SCREEN_D4: SCREEN.D4, SLAVE_DEBUG.28
SCREEN_D5: SCREEN.D5, SLAVE_DEBUG.29 (29/PWM)
SCREEN_D6: SCREEN.D6, SLAVE_DEBUG.30 (30/PWM)
SCREEN_D7: SCREEN.D7, SLAVE_DEBUG.31 (31/A12/RX4/CS1)
SCREEN_RD: SCREEN.RD, SLAVE_DEBUG.19 (19/A5/SCL0)
SCREEN_WR: SCREEN.WR, SLAVE_DEBUG.20 (20/A6/PWM/CS0)
SCREEN_X+: SCREEN.X+_2, SLAVE_DEBUG.15 (15/A1/CS0)
SCREEN_X-: SCREEN.X-_2, SLAVE_DEBUG.16 (16/A2)
SCREEN_Y+: SCREEN.Y+_2, SLAVE_DEBUG.17 (17/A3)
SCREEN_Y-: SCREEN.Y-_2, SLAVE_DEBUG.18 (18/A4/SDA0)
VIN: U$1.27 (VIN)
V_BAT: R1.2, R2.1, SLAVE_DEBUG.DA1 (A22/DAC1)

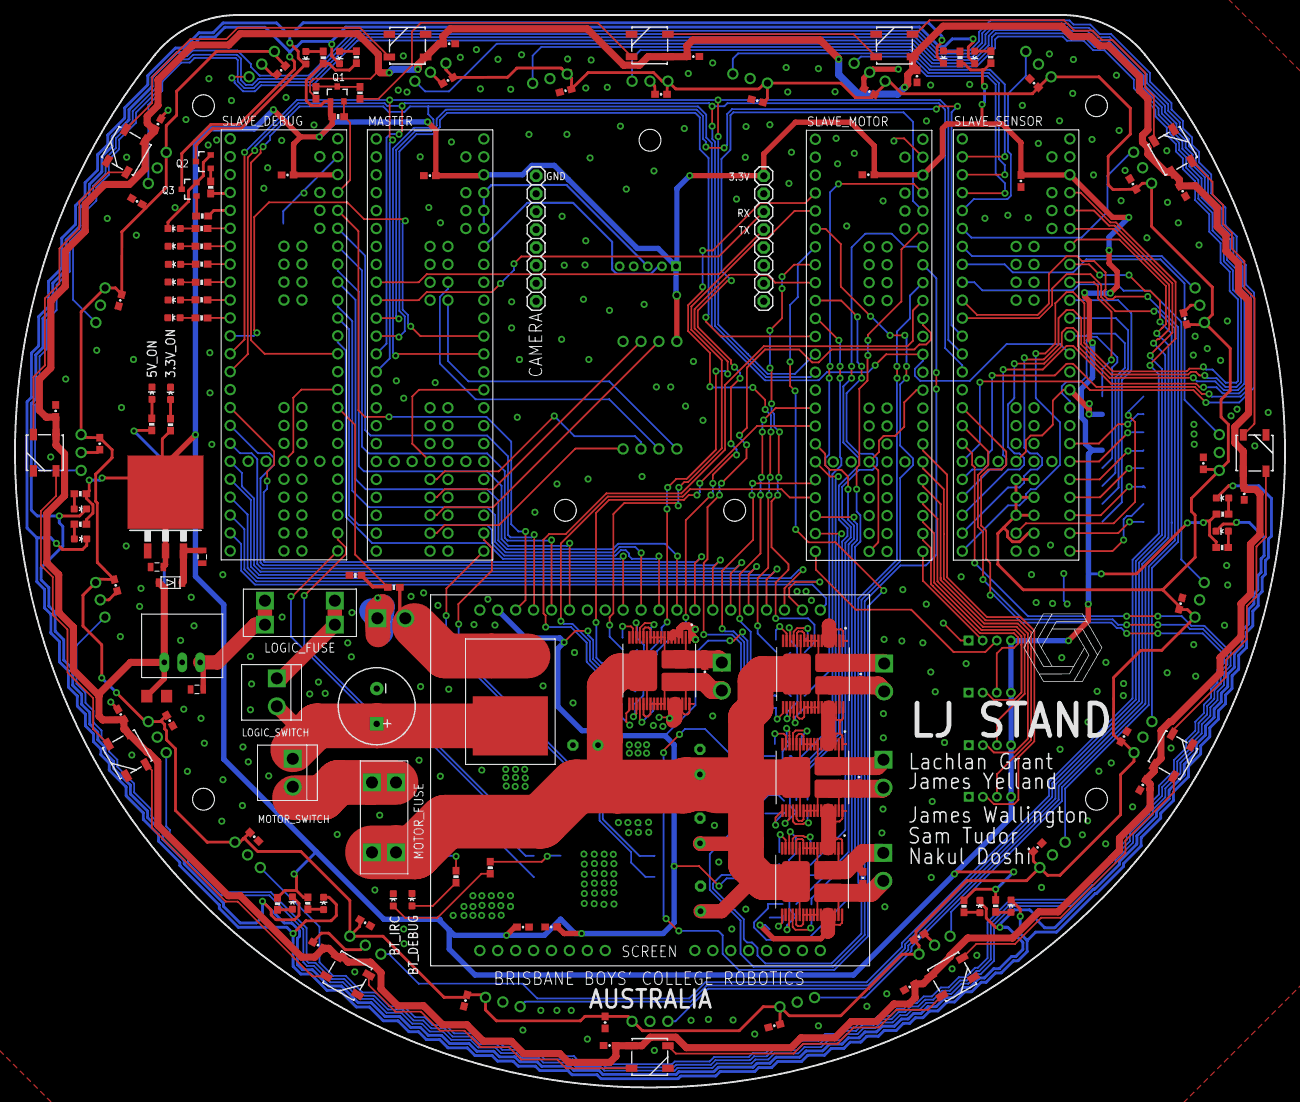
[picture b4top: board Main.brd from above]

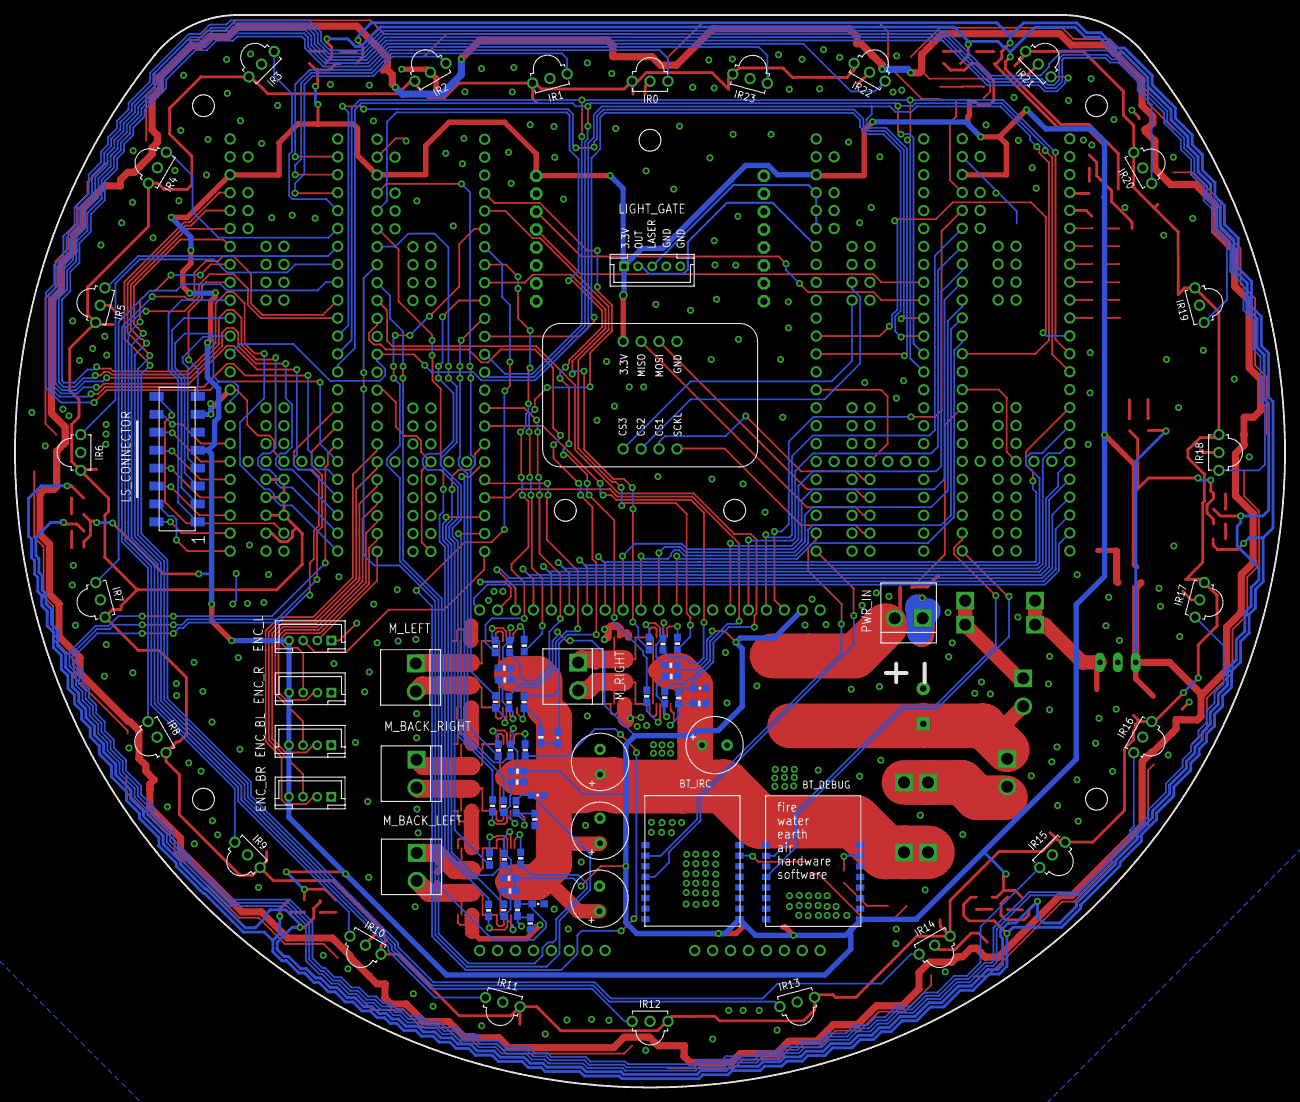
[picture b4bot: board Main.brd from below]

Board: 2 copper layers, 180.0 x 152.0 mm, 217 parts (82 on the bottom side), 199 nets.

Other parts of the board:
C20, C21, C22, C23: 0.1uF; 0603-CAP

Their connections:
MOTOR1_OUTA: C20.1; also elsewhere on the board
MOTOR1_OUTB: C20.2; also elsewhere on the board
MOTOR2_OUTA: C21.1; also elsewhere on the board
MOTOR2_OUTB: C21.2; also elsewhere on the board
MOTOR3_OUTA: C23.1; also elsewhere on the board
MOTOR3_OUTB: C23.2; also elsewhere on the board
MOTOR4_OUTA: C22.1; also elsewhere on the board
MOTOR4_OUTB: C22.2; also elsewhere on the board

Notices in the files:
parts and their libraries:
SparkFun-Resistors: Licensing: Creative Commons ShareAlike 4.0 International - https://creativecommons.org/licenses/by-sa/4.0
